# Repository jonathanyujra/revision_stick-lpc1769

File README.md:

# revision_stick-lpc1769
Módulo Stick LPC1769

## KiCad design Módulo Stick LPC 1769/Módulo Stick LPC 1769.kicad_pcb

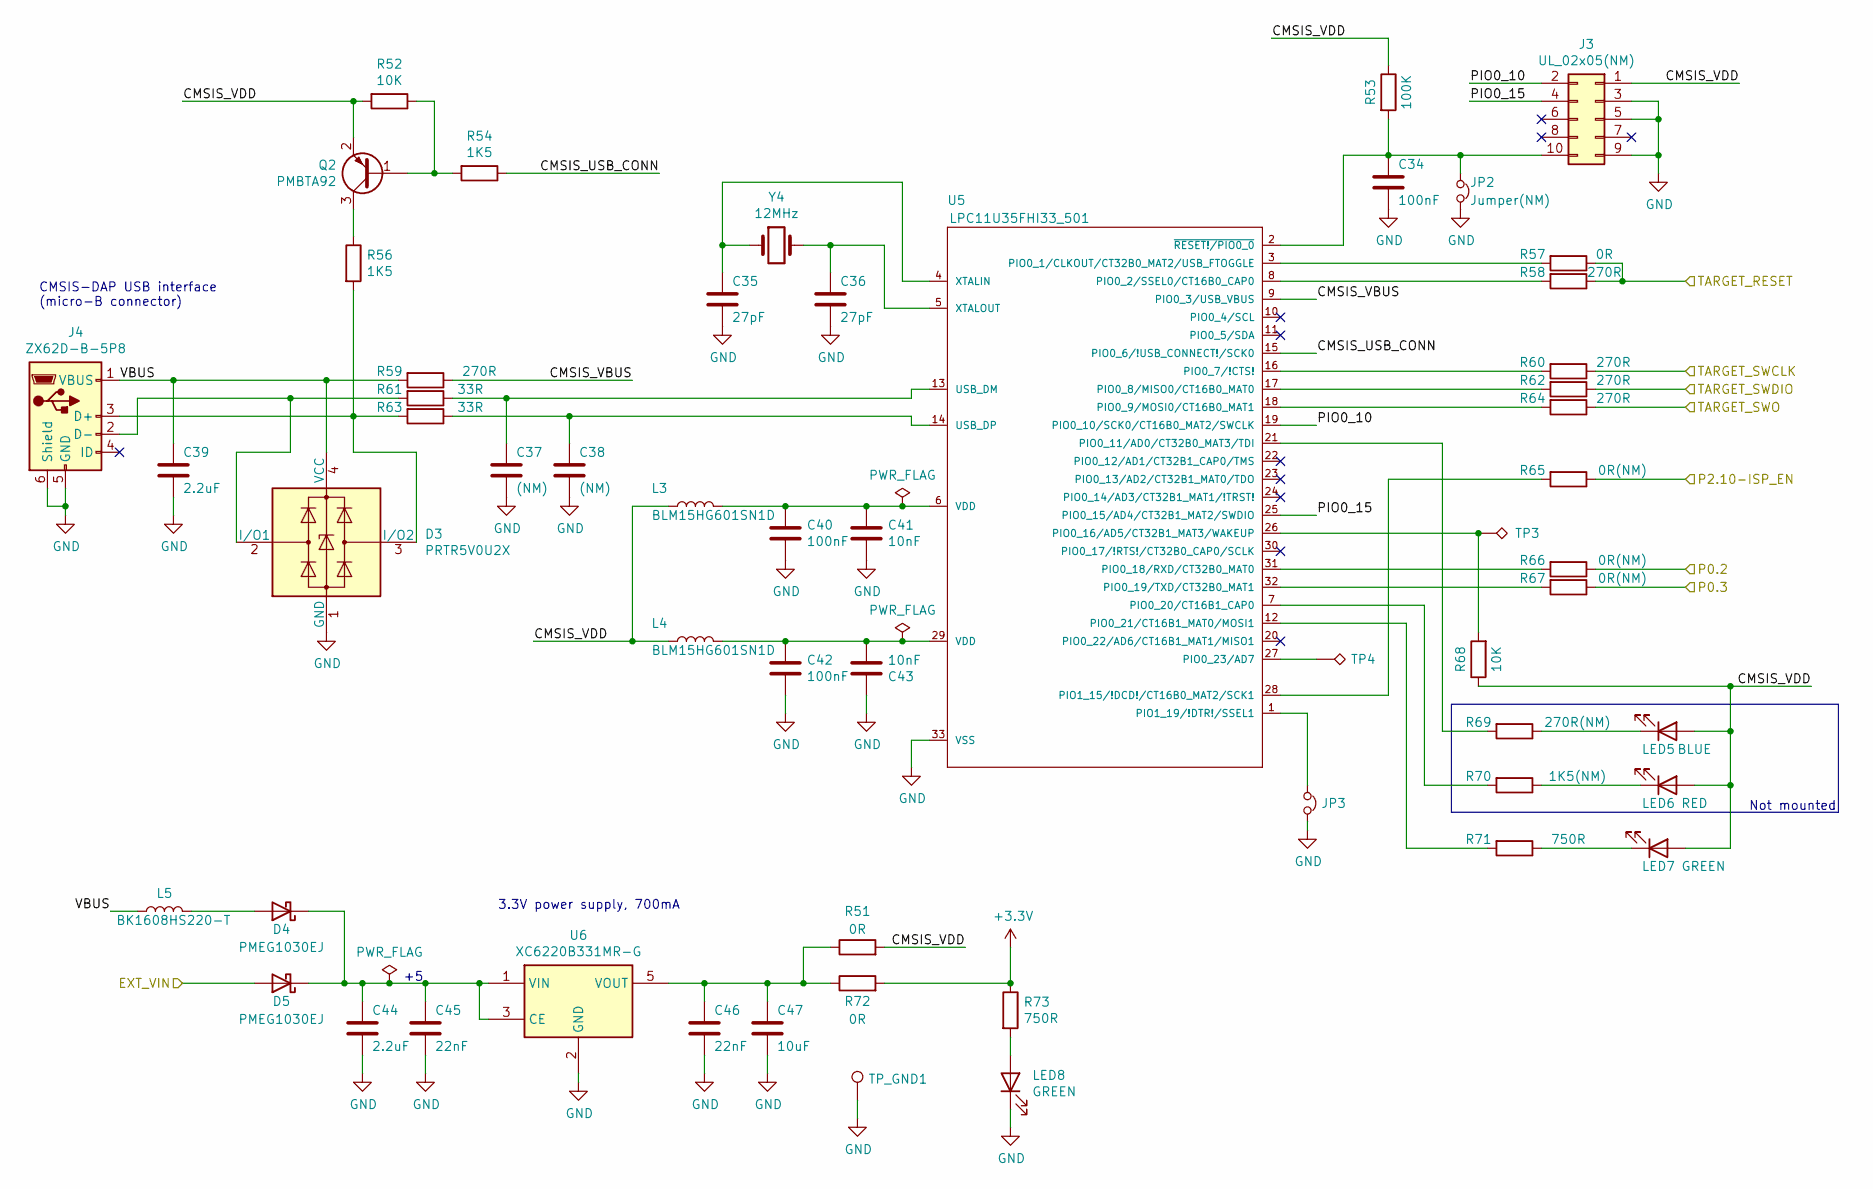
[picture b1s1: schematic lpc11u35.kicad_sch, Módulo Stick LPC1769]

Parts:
C34, C40, C42: 100nF; C_0603; Manufacturer P/N C0603C104Z3VACTU; Digi-Key P/N 399-1100-1-ND
C35, C36: 27pF; C_0603; Manufacturer P/N C0603C270J5GACTU; Digi-Key P/N 399-1054-1-ND
C37, C38: (NM); C_0603
C39, C44: 2.2uF; C_0805; Manufacturer P/N C0805C225K3RAC7800; Digi-Key P/N 399-11941-1-ND
C41, C43: 10nF; C_0603; Manufacturer P/N C0603C103K3RACTU; Digi-Key P/N 399-7840-1-ND
C45, C46: 22nF; C_0603; Manufacturer P/N C0603C223K3RACTU; Digi-Key P/N 399-1094-1-ND
C47: 10uF; C_0805; Manufacturer P/N C0805C106K3PAC7800; Digi-Key P/N 399-11939-1-ND
D3: PRTR5V0U2X; SOT-143; Manufacturer P/N PRTR5V0U2X,215; Digi-Key P/N 1727-3884-1-ND
D4, D5: PMEG1030EJ; D_SOD-323F; Manufacturer P/N PMEG1030EJ,115; Digi-Key P/N 1727-3852-1-ND
J3: UL_02x05(NM); M50-3600542
J4: ZX62D-B-5P8; USB_Micro-B; Manufacturer P/N 10118193-0001LF; Digi-Key P/N 609-4616-2-ND
JP2: Jumper(NM); Pin_Header_Straight_1x02_Pitch2.54mm
JP3: Jumper; Pin_Header_Straight_1x02_Pitch2.54mm_SMD_Pin1Right; Manufacturer P/N M50-3630242; Digi-Key P/N 952-3606-ND
L3, L4: BLM15HG601SN1D; L_0402; Manufacturer P/N BLM15HG601SN1D; Digi-Key P/N 490-3998-1-ND
L5: BK1608HS220-T; L_0603; Manufacturer P/N BK1608HS220-T; Digi-Key P/N 587-1869-1-ND
LED5: BLUE; LED_0603; Manufacturer P/N 150060BS55040; Digi-Key P/N 732-12013-1-ND
LED6: RED; LED_0603; Manufacturer P/N 150060RS55040; Digi-Key P/N 732-12015-1-ND
LED7, LED8: GREEN; LED_0603; Manufacturer P/N 150060VS55040; Digi-Key P/N 732-12017-1-ND
Q2: PMBTA92; SOT-23; Manufacturer P/N PMBTA92,215; Digi-Key P/N 1727-2966-1-ND
R51, R57, R72: 0R; R_0603; Manufacturer P/N RC0603JR-070RL; Digi-Key P/N 311-0.0GRCT-ND
R52, R68: 10K; R_0603; Manufacturer P/N RC0603JR-0710KL; Digi-Key P/N 311-10KGRCT-ND
R53: 100K; R_0603; Manufacturer P/N RC0603JR-07100KL; Digi-Key P/N 311-100KGRCT-ND
R54, R56: 1K5; R_0603; Manufacturer P/N RC0603JR-071K5L; Digi-Key P/N 311-1.5KGRCT-ND
R58, R59, R60, R62, R64: 270R; R_0603; Manufacturer P/N RC0603JR-07270RL; Digi-Key P/N 311-270GRCT-ND
R61, R63: 33R; R_0603; Manufacturer P/N RC0603JR-0733RL; Digi-Key P/N 311-33GRCT-ND
R65, R66, R67: 0R(NM); R_0603
R69: 270R(NM); R_0603
R70: 1K5(NM); R_0603
R71, R73: 750R; R_0603; Manufacturer P/N RC0603JR-07750RL; Digi-Key P/N 311-750GRCT-ND
TP3, TP4: TestPoint; TestPoint-SMD-S
TP_GND1: TestPoint; TestPoint-SMD-S
U5: LPC11U35FHI33_501; QFN65-8X8_M-33N; Manufacturer P/N LPC11U35FHI33/501; Digi-Key P/N 568-9586-ND
U6: XC6220B331MR-G; SOT-25; Manufacturer P/N XC6220B331MR-G; Digi-Key P/N 893-1133-1-ND
Y4: 12MHz; Crystal_SMD_HC49-SD; Manufacturer P/N ECS-120-20-5PX-TR; Digi-Key P/N XC2080CT-ND

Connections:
+3V3: R72.2, R73.1; also elsewhere on the board
/EXT_VIN: D5.2 (A); also elsewhere on the board
/LPC11U35/CMSIS_USB_CONN: R54.1, U5.15 (PIO0_6/!USB_CONNECT!/SCK0)
/LPC11U35/CMSIS_VBUS: R59.1, U5.9 (PIO0_3/USB_VBUS)
/LPC11U35/CMSIS_VDD: J3.1, L3.1, L4.1, LED5.2 (A), LED6.2 (A), LED7.2 (A), Q2.2 (E), R51.2, R52.2, R53.1, R68.1
/LPC11U35/PIO0_10: J3.2, U5.19 (PIO0_10/SCK0/CT16B0_MAT2/SWCLK)
/LPC11U35/PIO0_15: J3.4, U5.25 (PIO0_15/AD4/CT32B1_MAT2/SWDIO)
/LPC11U35/TARGET_SWCLK: R60.1; also elsewhere on the board
/LPC11U35/TARGET_SWDIO: R62.1; also elsewhere on the board
/LPC11U35/TARGET_SWO: R64.1; also elsewhere on the board
/P0.2: R66.1; also elsewhere on the board
/P0.3: R67.1; also elsewhere on the board
/P2.10-ISP_EN: R65.1; also elsewhere on the board
/TARGET_RESET: R57.1, R58.1; also elsewhere on the board
GND: C34.2, C35.2, C36.2, C37.2, C38.2, C39.2, C40.2, C41.2, C42.2, C43.1, C44.2, C45.2, C46.2, C47.2, D3.1 (GND), J3.3, J3.5, J3.9, J4.5 (GND), J4.6 (Shield), JP2.2, JP3.2, LED8.1 (K), TP_GND1.1, U5.33 (VSS), U6.2 (GND); also elsewhere on the board
unnamed: C34.1, J3.10, JP2.1, R53.2, U5.2 (~RESET!/PIO0_0)
unnamed: C35.1, U5.4 (XTALIN), Y4.1
unnamed: C36.1, U5.5 (XTALOUT), Y4.2
unnamed: C37.1, R61.1, U5.13 (USB_DM)
unnamed: C38.1, R63.1, U5.14 (USB_DP)
unnamed: C39.1, D3.4 (VCC), J4.1 (VBUS), L5.1, R59.2
unnamed: C40.1, C41.1, L3.2, U5.6 (VDD)
unnamed: C42.1, C43.2, L4.2, U5.29 (VDD)
unnamed: C44.1, C45.1, D4.1 (K), D5.1 (K), U6.1 (VIN), U6.3 (CE)
unnamed: C46.1, C47.1, R51.1, R72.1, U6.5 (VOUT)
unnamed: D3.2 (I/O1), J4.2 (D-), R61.2
unnamed: D3.3 (I/O2), J4.3 (D+), R56.2, R63.2
unnamed: D4.2 (A), L5.2
unnamed: JP3.1, U5.1 (PIO1_19/!DTR!/SSEL1)
unnamed: LED5.1 (K), R69.1
unnamed: LED6.1 (K), R70.1
unnamed: LED7.1 (K), R71.1
unnamed: LED8.2 (A), R73.2
unnamed: Q2.1 (B), R52.1, R54.2
unnamed: Q2.3 (C), R56.1
unnamed: R57.2, U5.3 (PIO0_1/CLKOUT/CT32B0_MAT2/USB_FTOGGLE)
unnamed: R58.2, U5.8 (PIO0_2/SSEL0/CT16B0_CAP0)
unnamed: R60.2, U5.16 (PIO0_7/!CTS!)
unnamed: R62.2, U5.17 (PIO0_8/MISO0/CT16B0_MAT0)
unnamed: R64.2, U5.18 (PIO0_9/MOSI0/CT16B0_MAT1)
unnamed: R65.2, U5.28 (PIO1_15/!DCD!/CT16B0_MAT2/SCK1)
unnamed: R66.2, U5.31 (PIO0_18/RXD/CT32B0_MAT0)
unnamed: R67.2, U5.32 (PIO0_19/TXD/CT32B0_MAT1)
unnamed: R68.2, TP3.1, U5.26 (PIO0_16/AD5/CT32B1_MAT3/WAKEUP)
unnamed: R69.2, U5.21 (PIO0_11/AD0/CT32B0_MAT3/TDI)
unnamed: R70.2, U5.7 (PIO0_20/CT16B1_CAP0)
unnamed: R71.2, U5.12 (PIO0_21/CT16B1_MAT0/MOSI1)
unnamed: TP4.1, U5.27 (PIO0_23/AD7)

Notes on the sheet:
CMSIS-DAP USB interface (micro-B connector)
3.3V power supply, 700mA
Not mounted

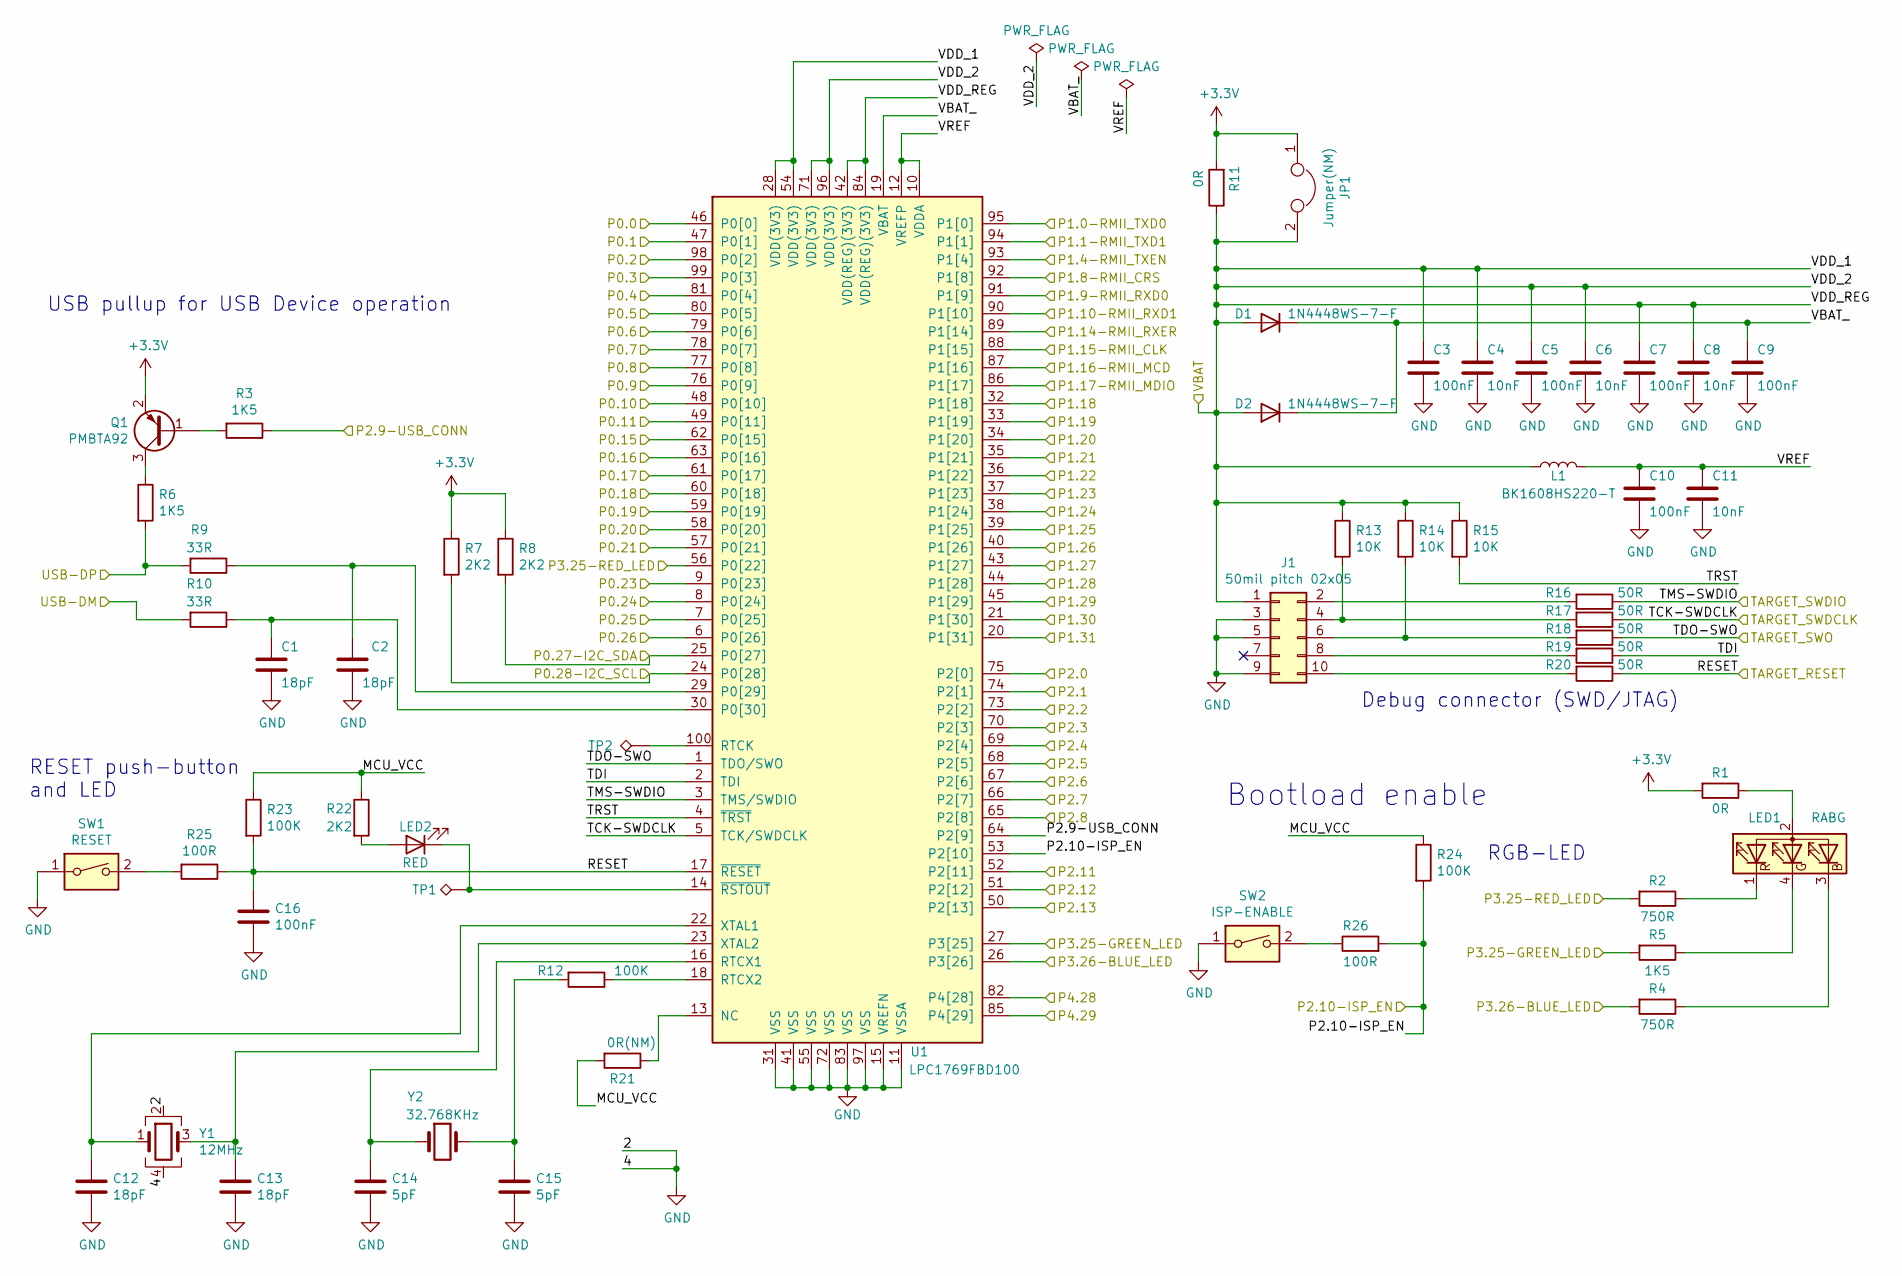
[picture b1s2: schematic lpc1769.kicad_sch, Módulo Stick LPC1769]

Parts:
C1, C2, C12, C13: 18pF; C_0603; Manufacturer P/N C0603C180J5GACTU; Digi-Key P/N 399-1052-1-ND
C3, C5, C7, C9, C10, C16: 100nF; C_0603; Manufacturer P/N C0603C104Z3VACTU; Digi-Key P/N 399-1100-1-ND
C4, C6, C8, C11: 10nF; C_0603; Manufacturer P/N C0603C103K3RACTU; Digi-Key P/N 399-7840-1-ND
C14, C15: 5pF; C_0603; Manufacturer P/N CBR06C509C5GAC; Digi-Key P/N 399-17324-1-ND
D1, D2: 1N4448WS-7-F; D_SOD-323; Manufacturer P/N 1N4448WS-7-F; Digi-Key P/N 1N4448WS-FDICT-ND
J1: 50mil pitch 02x05; M50-3600542; Manufacturer P/N M50-3600542; Digi-Key P/N 952-1389-ND
JP1: Jumper(NM); Pin_Header_Straight_1x02_Pitch2.54mm
L1: BK1608HS220-T; L_0603; Manufacturer P/N BK1608HS220-T; Digi-Key P/N 587-1869-1-ND
LED1: RABG; LED_RGB_1210; Manufacturer P/N AAA3528SEEZGKQBKS; Digi-Key P/N 754-1973-1-ND
LED2: RED; LED_0603; Manufacturer P/N 150060RS55040; Digi-Key P/N 732-12015-1-ND
Q1: PMBTA92; SOT-23; Manufacturer P/N PMBTA92,215; Digi-Key P/N 1727-2966-1-ND
R1, R11: 0R; R_0603; Manufacturer P/N RC0603JR-070RL; Digi-Key P/N 311-0.0GRCT-ND
R2, R4: 750R; R_0603; Manufacturer P/N RC0603JR-07750RL; Digi-Key P/N 311-750GRCT-ND
R3, R5, R6: 1K5; R_0603; Manufacturer P/N RC0603JR-071K5L; Digi-Key P/N 311-1.5KGRCT-ND
R7, R8, R22: 2K2; R_0603; Manufacturer P/N RC0603JR-072K2L; Digi-Key P/N 311-2.2KGRCT-ND
R9, R10: 33R; R_0603; Manufacturer P/N RC0603JR-0733RL; Digi-Key P/N 311-33GRCT-ND
R12, R23, R24: 100K; R_0603; Manufacturer P/N RC0603JR-07100KL; Digi-Key P/N 311-100KGRCT-ND
R13, R14, R15: 10K; R_0603; Manufacturer P/N RC0603JR-0710KL; Digi-Key P/N 311-10KGRCT-ND
R16, R17, R18, R19, R20: 50R; R_0603; Manufacturer P/N CRCW060350R0FKEA; Digi-Key P/N 541-3318-1-ND
R21: 0R(NM); R_0603
R25, R26: 100R; R_0603; Manufacturer P/N RC0603JR-07100RL; Digi-Key P/N 311-100GRCT-ND
SW1: RESET; SW_2.80x4.60mm; Manufacturer P/N TL6330AF200Q; Digi-Key P/N EG5546CT-ND
SW2: ISP-ENABLE; SW_2.80x4.60mm; Manufacturer P/N TL6330AF200Q; Digi-Key P/N EG5546CT-ND
TP1, TP2: TestPoint; TestPoint-SMD-S
U1: LPC1769FBD100; Manufacturer P/N LPC1769FBD100,551; Digi-Key P/N 568-4966-ND
Y1: 12MHz; Crystal_SMD_3225-4pin_3.2x2.5mm; Manufacturer P/N ECS-120-18-33-AGN-TR; Digi-Key P/N XC2910CT-ND
Y2: 32.768KHz; Crystal_SMD_SeikoEpson_MC146-4pin_6.7x1.5mm; Manufacturer P/N MC-146 32.7680KA-A5: PURE SN; Digi-Key P/N SER4301CT-ND

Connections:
+3V3: JP1.1, Q1.2 (E), R1.2, R7.1, R8.1, R11.2; also elsewhere on the board
/Expansion_connector/P0.15: U1.62 (P0[15]); also elsewhere on the board
/Expansion_connector/P0.16: U1.63 (P0[16]); also elsewhere on the board
/Expansion_connector/P0.17: U1.61 (P0[17]); also elsewhere on the board
/Expansion_connector/P0.18: U1.60 (P0[18]); also elsewhere on the board
/Expansion_connector/P0.21: U1.57 (P0[21]); also elsewhere on the board
/Expansion_connector/P0.22-RED_LED: R2.2, U1.56 (P0[22]); also elsewhere on the board
/Expansion_connector/P0.23: U1.9 (P0[23]); also elsewhere on the board
/Expansion_connector/P0.24: U1.8 (P0[24]); also elsewhere on the board
/Expansion_connector/P0.25: U1.7 (P0[25]); also elsewhere on the board
/Expansion_connector/P0.26: U1.6 (P0[26]); also elsewhere on the board
/Expansion_connector/P0.27-I2C_SDA: R8.2, U1.25 (P0[27]); also elsewhere on the board
/Expansion_connector/P0.28-I2C_SCL: R7.2, U1.24 (P0[28]); also elsewhere on the board
/Expansion_connector/P1.18: U1.32 (P1[18]); also elsewhere on the board
/Expansion_connector/P1.19: U1.33 (P1[19]); also elsewhere on the board
/Expansion_connector/P1.20: U1.34 (P1[20]); also elsewhere on the board
/Expansion_connector/P1.21: U1.35 (P1[21]); also elsewhere on the board
/Expansion_connector/P1.22: U1.36 (P1[22]); also elsewhere on the board
/Expansion_connector/P1.23: U1.37 (P1[23]); also elsewhere on the board
/Expansion_connector/P1.24: U1.38 (P1[24]); also elsewhere on the board
/Expansion_connector/P1.25: U1.39 (P1[25]); also elsewhere on the board
/Expansion_connector/P1.26: U1.40 (P1[26]); also elsewhere on the board
/Expansion_connector/P1.27: U1.43 (P1[27]); also elsewhere on the board
/Expansion_connector/P1.28: U1.44 (P1[28]); also elsewhere on the board
/Expansion_connector/P1.29: U1.45 (P1[29]); also elsewhere on the board
/Expansion_connector/P1.30: U1.21 (P1[30]); also elsewhere on the board
/Expansion_connector/P1.31: U1.20 (P1[31]); also elsewhere on the board
/Expansion_connector/P2.0: U1.75 (P2[0]); also elsewhere on the board
/Expansion_connector/P2.1: U1.74 (P2[1]); also elsewhere on the board
/Expansion_connector/P2.2: U1.73 (P2[2]); also elsewhere on the board
/Expansion_connector/P2.3: U1.70 (P2[3]); also elsewhere on the board
/Expansion_connector/P2.4: U1.69 (P2[4]); also elsewhere on the board
/Expansion_connector/P2.5: U1.68 (P2[5]); also elsewhere on the board
/Expansion_connector/P2.6: U1.67 (P2[6]); also elsewhere on the board
/Expansion_connector/P2.7: U1.66 (P2[7]); also elsewhere on the board
/Expansion_connector/P2.8: U1.65 (P2[8]); also elsewhere on the board
/Expansion_connector/P2.11: U1.52 (P2[11]); also elsewhere on the board
/Expansion_connector/P2.12: U1.51 (P2[12]); also elsewhere on the board
/Expansion_connector/P2.13: U1.50 (P2[13]); also elsewhere on the board
/Expansion_connector/P3.25-GREEN_LED: R5.2, U1.27 (P3[25]); also elsewhere on the board
/Expansion_connector/P3.26-BLUE_LED: R4.2, U1.26 (P3[26]); also elsewhere on the board
/Expansion_connector/P4.28: U1.82 (P4[28]); also elsewhere on the board
/Expansion_connector/P4.29: U1.85 (P4[29]); also elsewhere on the board
/LAN8720/P1.0-RMII_TXD0: U1.95 (P1[0]); also elsewhere on the board
/LAN8720/P1.1-RMII_TXD1: U1.94 (P1[1]); also elsewhere on the board
/LAN8720/P1.4-RMII_TXEN: U1.93 (P1[4]); also elsewhere on the board
/LAN8720/P1.8-RMII_CRS: U1.92 (P1[8]); also elsewhere on the board
/LAN8720/P1.9-RMII_RXD0: U1.91 (P1[9]); also elsewhere on the board
/LAN8720/P1.10-RMII_RXD1: U1.90 (P1[10]); also elsewhere on the board
/LAN8720/P1.14-RMII_RXER: U1.89 (P1[14]); also elsewhere on the board
/LAN8720/P1.15-RMII_CLK: U1.88 (P1[15]); also elsewhere on the board
/LAN8720/P1.16-RMII_MCD: U1.87 (P1[16]); also elsewhere on the board
/LAN8720/P1.17-RMII_MDIO: U1.86 (P1[17]); also elsewhere on the board
/LPC11U35/TARGET_SWCLK: R17.1, U1.5 (TCK/SWDCLK); also elsewhere on the board
/LPC11U35/TARGET_SWDIO: R16.1, U1.3 (TMS/SWDIO); also elsewhere on the board
/LPC11U35/TARGET_SWO: R18.1, U1.1 (TDO/SWO); also elsewhere on the board
/LPC1769/MCU_VCC: R21.2, R22.1, R23.1, R24.1
/LPC1769/TDI: R19.1, U1.2 (TDI)
/LPC1769/TRST: R15.2, U1.4 (~TRST)
/LPC1769/VBAT_: C9.1, D1.1 (K), D2.1 (K), U1.19 (VBAT)
/LPC1769/VREF: C10.1, C11.1, L1.2, U1.10 (VDDA), U1.12 (VREFP)
/P0.0: U1.46 (P0[0]); also elsewhere on the board
/P0.1: U1.47 (P0[1]); also elsewhere on the board
/P0.2: U1.98 (P0[2]); also elsewhere on the board
/P0.3: U1.99 (P0[3]); also elsewhere on the board
/P0.4: U1.81 (P0[4]); also elsewhere on the board
/P0.5: U1.80 (P0[5]); also elsewhere on the board
/P0.6: U1.79 (P0[6]); also elsewhere on the board
/P0.7: U1.78 (P0[7]); also elsewhere on the board
/P0.8: U1.77 (P0[8]); also elsewhere on the board
/P0.9: U1.76 (P0[9]); also elsewhere on the board
/P0.10: U1.48 (P0[10]); also elsewhere on the board
/P0.11: U1.49 (P0[11]); also elsewhere on the board
/P0.19: U1.59 (P0[19]); also elsewhere on the board
/P0.20: U1.58 (P0[20]); also elsewhere on the board
/P2.9-USB_CONN: R3.1, U1.64 (P2[9]); also elsewhere on the board
/P2.10-ISP_EN: R24.2, R26.2, U1.53 (P2[10]); also elsewhere on the board
/TARGET_RESET: C16.1, R20.1, R23.2, R25.1, U1.17 (~RESET); also elsewhere on the board
/USB-DM: R10.2; also elsewhere on the board
/USB-DP: R6.2, R9.2; also elsewhere on the board
GND: C1.2, C2.2, C3.2, C4.2, C5.2, C6.2, C7.2, C8.2, C9.2, C10.2, C11.2, C12.2, C13.2, C14.2, C15.2, C16.2, J1.3, J1.5, J1.9, SW1.1, SW2.1, U1.11 (VSSA), U1.15 (VREFN), U1.31 (VSS), U1.41 (VSS), U1.55 (VSS), U1.72 (VSS), U1.83 (VSS), U1.97 (VSS), Y1.2, Y1.4; also elsewhere on the board
unnamed: C1.1, R10.1, U1.30 (P0[30])
unnamed: C2.1, R9.1, U1.29 (P0[29])
unnamed: C12.1, U1.22 (XTAL1), Y1.1
unnamed: C13.1, U1.23 (XTAL2), Y1.3
unnamed: C14.1, U1.16 (RTCX1), Y2.1
unnamed: C15.1, R12.2, Y2.2
unnamed: J1.2, R16.2
unnamed: J1.4, R13.2, R17.2
unnamed: J1.6, R14.2, R18.2
unnamed: J1.8, R19.2
unnamed: J1.10, R20.2
unnamed: LED1.1 (RK), R2.1
unnamed: LED1.2 (A), R1.1
unnamed: LED1.3 (BK), R4.1
unnamed: LED1.4 (GK), R5.1
unnamed: LED2.1 (K), TP1.1, U1.14 (~RSTOUT)
unnamed: LED2.2 (A), R22.2
unnamed: Q1.1 (B), R3.2
unnamed: Q1.3 (C), R6.1
unnamed: R12.1, U1.18 (RTCX2)
unnamed: R21.1, U1.13 (NC)
unnamed: R25.2, SW1.2
unnamed: R26.1, SW2.2
unnamed: TP2.1, U1.100 (RTCK)

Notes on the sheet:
Debug connector (SWD/JTAG)
RGB-LED
USB pullup for USB Device operation
RESET push-button and LED
Bootload enable

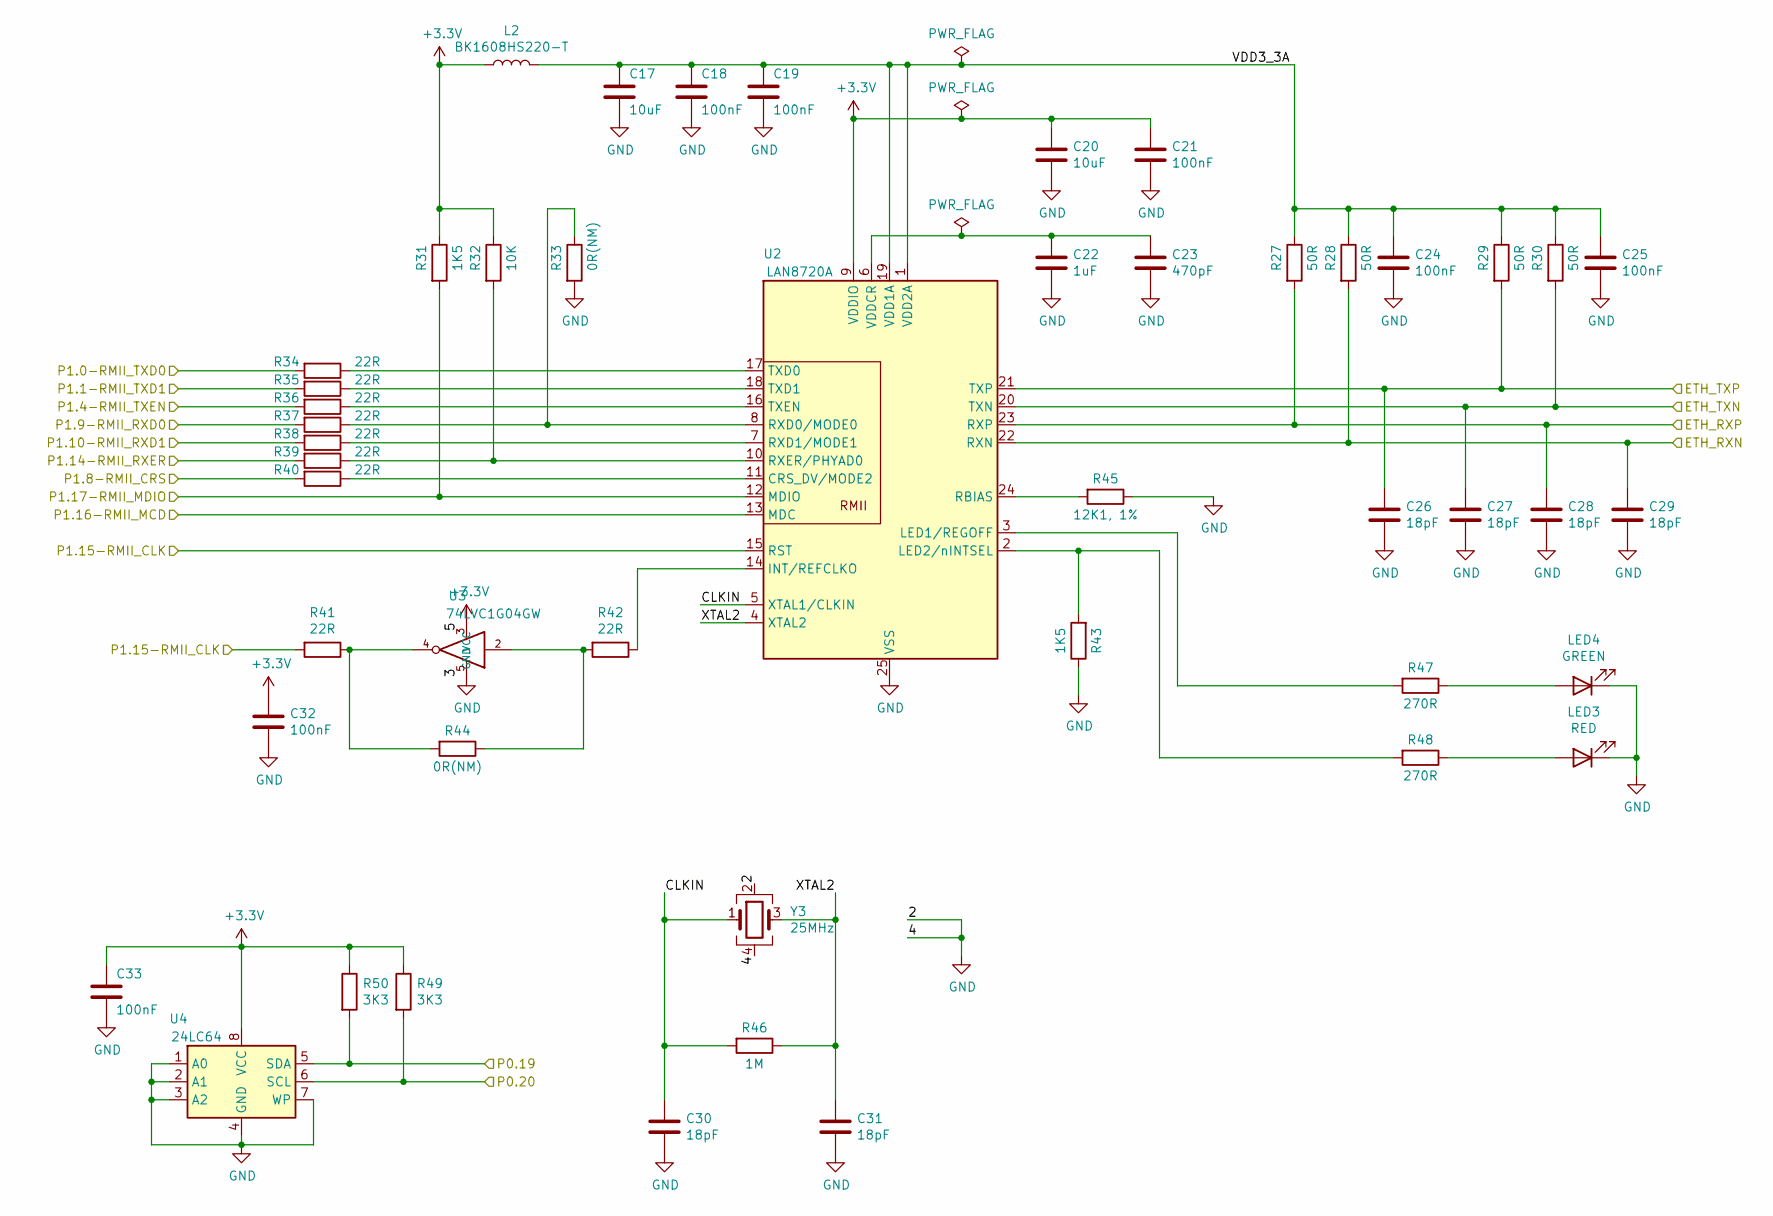
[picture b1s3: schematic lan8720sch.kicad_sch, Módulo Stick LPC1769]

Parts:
C17, C20: 10uF; C_0805; Manufacturer P/N C0805C106K3PAC7800; Digi-Key P/N 399-11939-1-ND
C18, C19, C21, C24, C25, C32, C33: 100nF; C_0603; Manufacturer P/N C0603C104Z3VACTU; Digi-Key P/N 399-1100-1-ND
C22: 1uF; C_0805; Manufacturer P/N C0805C105K3RACTU; Digi-Key P/N 399-8004-1-ND
C23: 470pF; C_0603; Manufacturer P/N C0603C471K5RACTU; Digi-Key P/N 399-1075-1-ND
C26, C27, C28, C29, C30, C31: 18pF; C_0603; Manufacturer P/N C0603C180J5GACTU; Digi-Key P/N 399-1052-1-ND
L2: BK1608HS220-T; L_0603; Manufacturer P/N BK1608HS220-T; Digi-Key P/N 587-1869-1-ND
LED3: RED; LED_0603; Manufacturer P/N 150060RS55040; Digi-Key P/N 732-12015-1-ND
LED4: GREEN; LED_0603; Manufacturer P/N 150060VS55040; Digi-Key P/N 732-12017-1-ND
R27, R28, R29, R30: 50R; R_0603; Manufacturer P/N CRCW060350R0FKEA; Digi-Key P/N 541-3318-1-ND
R31, R43: 1K5; R_0603; Manufacturer P/N RC0603JR-071K5L; Digi-Key P/N 311-1.5KGRCT-ND
R32: 10K; R_0603; Manufacturer P/N RC0603JR-0710KL; Digi-Key P/N 311-10KGRCT-ND
R33, R44: 0R(NM); R_0603
R34, R35, R36, R37, R38, R39, R40, R41, R42: 22R; R_0603; Manufacturer P/N RC0603JR-0722RL; Digi-Key P/N 311-22GRCT-ND
R45: 12K1, 1%; R_0603; Manufacturer P/N RC0603FR-0712K1L; Digi-Key P/N 311-12.1KHRCT-ND
R46: 1M; R_0603; Manufacturer P/N RC0603JR-071ML; Digi-Key P/N 311-1.0MGRCT-ND
R47, R48: 270R; R_0603; Manufacturer P/N RC0603JR-07270RL; Digi-Key P/N 311-270GRCT-ND
R49, R50: 3K3; R_0603; Manufacturer P/N RC0603JR-073K3L; Digi-Key P/N 311-3.3KGRCT-ND
U2: LAN8720A; LAN8720A-CP; Manufacturer P/N LAN8720A-CP; Digi-Key P/N 638-1080-ND
U3: 74LVC1G04GW; SOT-353_SC-70-5; Manufacturer P/N 74LVC1G04GW,125; Digi-Key P/N 1727-2871-1-ND
U4: 24LC64; 24LC64T-I&slash_SN; Manufacturer P/N 24LC64T-I/SN; Digi-Key P/N 24LC64T-I/SNCT-ND
Y3: 25MHz; Crystal_SMD_3225-4pin_3.2x2.5mm; Manufacturer P/N ECS-250-8-33-JGN-TR; Digi-Key P/N XC2650CT-ND

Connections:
+3V3: C20.1, C21.1, C32.1, C33.1, L2.1, R31.1, R32.1, R49.1, R50.1, U2.9 (VDDIO), U3.3 (GND), U4.8 (VCC); also elsewhere on the board
/ETH_RXN: C29.1, R28.2, U2.22 (RXN); also elsewhere on the board
/ETH_RXP: C28.1, R27.2, U2.23 (RXP); also elsewhere on the board
/ETH_TXN: C27.1, R30.2, U2.20 (TXN); also elsewhere on the board
/ETH_TXP: C26.1, R29.2, U2.21 (TXP); also elsewhere on the board
/LAN8720/P1.0-RMII_TXD0: R34.2; also elsewhere on the board
/LAN8720/P1.1-RMII_TXD1: R35.2; also elsewhere on the board
/LAN8720/P1.4-RMII_TXEN: R36.2; also elsewhere on the board
/LAN8720/P1.8-RMII_CRS: R40.2; also elsewhere on the board
/LAN8720/P1.9-RMII_RXD0: R37.2; also elsewhere on the board
/LAN8720/P1.10-RMII_RXD1: R38.2; also elsewhere on the board
/LAN8720/P1.14-RMII_RXER: R39.2; also elsewhere on the board
/LAN8720/P1.15-RMII_CLK: R41.2, U2.15 (RST); also elsewhere on the board
/LAN8720/P1.16-RMII_MCD: U2.13 (MDC); also elsewhere on the board
/LAN8720/P1.17-RMII_MDIO: R31.2, U2.12 (MDIO); also elsewhere on the board
/LAN8720/VDD3_3A: C17.1, C18.1, C19.1, C24.1, C25.1, L2.2, R27.1, R28.1, R29.1, R30.1, U2.1 (VDD2A), U2.19 (VDD1A)
/P0.19: R50.2, U4.5 (SDA); also elsewhere on the board
/P0.20: R49.2, U4.6 (SCL); also elsewhere on the board
GND: C17.2, C18.2, C19.2, C20.2, C21.2, C22.2, C23.2, C24.2, C25.2, C26.2, C27.2, C28.2, C29.2, C30.2, C31.2, C32.2, C33.2, LED3.1 (K), LED4.1 (K), R33.2, R43.1, R45.1, U2.25 (VSS), U3.5 (VCC), U4.1 (A0), U4.2 (A1), U4.3 (A2), U4.4 (GND), U4.7 (WP), Y3.2, Y3.4; also elsewhere on the board
unnamed: C22.1, C23.1, U2.6 (VDDCR)
unnamed: C30.1, R46.2, U2.5 (XTAL1/CLKIN), Y3.1
unnamed: C31.1, R46.1, U2.4 (XTAL2), Y3.3
unnamed: LED3.2 (A), R48.1
unnamed: LED4.2 (A), R47.1
unnamed: R32.2, R39.1, U2.10 (RXER/PHYAD0)
unnamed: R33.1, R37.1, U2.8 (RXD0/MODE0)
unnamed: R34.1, U2.17 (TXD0)
unnamed: R35.1, U2.18 (TXD1)
unnamed: R36.1, U2.16 (TXEN)
unnamed: R38.1, U2.7 (RXD1/MODE1)
unnamed: R40.1, U2.11 (CRS_DV/MODE2)
unnamed: R41.1, R44.2, U3.4
unnamed: R42.1, U2.14 (INT/REFCLKO)
unnamed: R42.2, R44.1, U3.2
unnamed: R43.2, R48.2, U2.2 (LED2/nINTSEL)
unnamed: R45.2, U2.24 (RBIAS)
unnamed: R47.2, U2.3 (LED1/REGOFF)

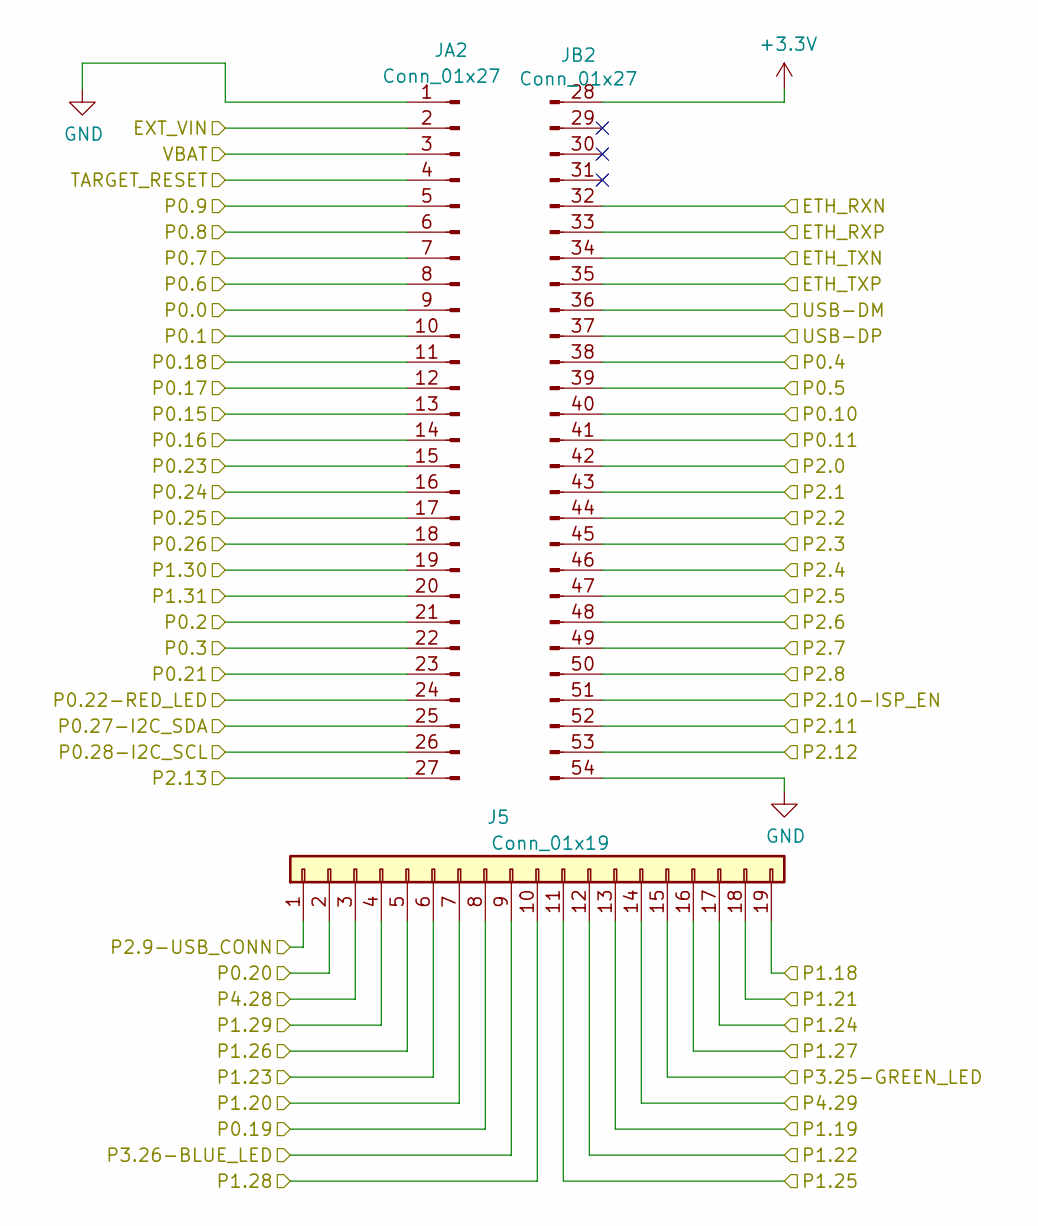
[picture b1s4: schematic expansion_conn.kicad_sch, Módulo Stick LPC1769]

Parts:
J5: Conn_01x19; conn_x19_Pitch2.54mm; Manufacturer P/N 0022284190; Digi-Key P/N WM50014-19-ND
JA2: Conn_01x27; J2_A_1x27_Pitch2.54mm; Manufacturer P/N 0022284270; Digi-Key P/N WM50014-27-ND
JB2: Conn_01x27; J2_B_01x27_Pitch2.54mm; Manufacturer P/N 0022284270; Digi-Key P/N WM50014-27-ND

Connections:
+3V3: JB2.28; also elsewhere on the board
/ETH_RXN: JB2.32; also elsewhere on the board
/ETH_RXP: JB2.33; also elsewhere on the board
/ETH_TXN: JB2.34; also elsewhere on the board
/ETH_TXP: JB2.35; also elsewhere on the board
/EXT_VIN: JA2.2; also elsewhere on the board
/Expansion_connector/P0.15: JA2.13; also elsewhere on the board
/Expansion_connector/P0.16: JA2.14; also elsewhere on the board
/Expansion_connector/P0.17: JA2.12; also elsewhere on the board
/Expansion_connector/P0.18: JA2.11; also elsewhere on the board
/Expansion_connector/P0.21: JA2.23; also elsewhere on the board
/Expansion_connector/P0.22-RED_LED: JA2.24; also elsewhere on the board
/Expansion_connector/P0.23: JA2.15; also elsewhere on the board
/Expansion_connector/P0.24: JA2.16; also elsewhere on the board
/Expansion_connector/P0.25: JA2.17; also elsewhere on the board
/Expansion_connector/P0.26: JA2.18; also elsewhere on the board
/Expansion_connector/P0.27-I2C_SDA: JA2.25; also elsewhere on the board
/Expansion_connector/P0.28-I2C_SCL: JA2.26; also elsewhere on the board
/Expansion_connector/P1.18: J5.19; also elsewhere on the board
/Expansion_connector/P1.19: J5.13; also elsewhere on the board
/Expansion_connector/P1.20: J5.7; also elsewhere on the board
/Expansion_connector/P1.21: J5.18; also elsewhere on the board
/Expansion_connector/P1.22: J5.12; also elsewhere on the board
/Expansion_connector/P1.23: J5.6; also elsewhere on the board
/Expansion_connector/P1.24: J5.17; also elsewhere on the board
/Expansion_connector/P1.25: J5.11; also elsewhere on the board
/Expansion_connector/P1.26: J5.5; also elsewhere on the board
/Expansion_connector/P1.27: J5.16; also elsewhere on the board
/Expansion_connector/P1.28: J5.10; also elsewhere on the board
/Expansion_connector/P1.29: J5.4; also elsewhere on the board
/Expansion_connector/P1.30: JA2.19; also elsewhere on the board
/Expansion_connector/P1.31: JA2.20; also elsewhere on the board
/Expansion_connector/P2.0: JB2.42 (Pin_12); also elsewhere on the board
/Expansion_connector/P2.1: JB2.43 (Pin_13); also elsewhere on the board
/Expansion_connector/P2.2: JB2.44 (Pin_14); also elsewhere on the board
/Expansion_connector/P2.3: JB2.45 (Pin_15); also elsewhere on the board
/Expansion_connector/P2.4: JB2.46 (Pin_16); also elsewhere on the board
/Expansion_connector/P2.5: JB2.47 (Pin_17); also elsewhere on the board
/Expansion_connector/P2.6: JB2.48 (Pin_18); also elsewhere on the board
/Expansion_connector/P2.7: JB2.49 (Pin_19); also elsewhere on the board
/Expansion_connector/P2.8: JB2.50 (Pin_20); also elsewhere on the board
/Expansion_connector/P2.11: JB2.52 (Pin_22); also elsewhere on the board
/Expansion_connector/P2.12: JB2.53 (Pin_23); also elsewhere on the board
/Expansion_connector/P2.13: JA2.27; also elsewhere on the board
/Expansion_connector/P3.25-GREEN_LED: J5.15; also elsewhere on the board
/Expansion_connector/P3.26-BLUE_LED: J5.9; also elsewhere on the board
/Expansion_connector/P4.28: J5.3; also elsewhere on the board
/Expansion_connector/P4.29: J5.14; also elsewhere on the board
/P0.0: JA2.9; also elsewhere on the board
/P0.1: JA2.10; also elsewhere on the board
/P0.2: JA2.21; also elsewhere on the board
/P0.3: JA2.22; also elsewhere on the board
/P0.4: JB2.38; also elsewhere on the board
/P0.5: JB2.39; also elsewhere on the board
/P0.6: JA2.8; also elsewhere on the board
/P0.7: JA2.7; also elsewhere on the board
/P0.8: JA2.6; also elsewhere on the board
/P0.9: JA2.5; also elsewhere on the board
/P0.10: JB2.40; also elsewhere on the board
/P0.11: JB2.41 (Pin_11); also elsewhere on the board
/P0.19: J5.8; also elsewhere on the board
/P0.20: J5.2; also elsewhere on the board
/P2.9-USB_CONN: J5.1; also elsewhere on the board
/P2.10-ISP_EN: JB2.51 (Pin_21); also elsewhere on the board
/TARGET_RESET: JA2.4; also elsewhere on the board
/USB-DM: JB2.36; also elsewhere on the board
/USB-DP: JB2.37; also elsewhere on the board
GND: JA2.1, JB2.54 (Pin_24); also elsewhere on the board

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
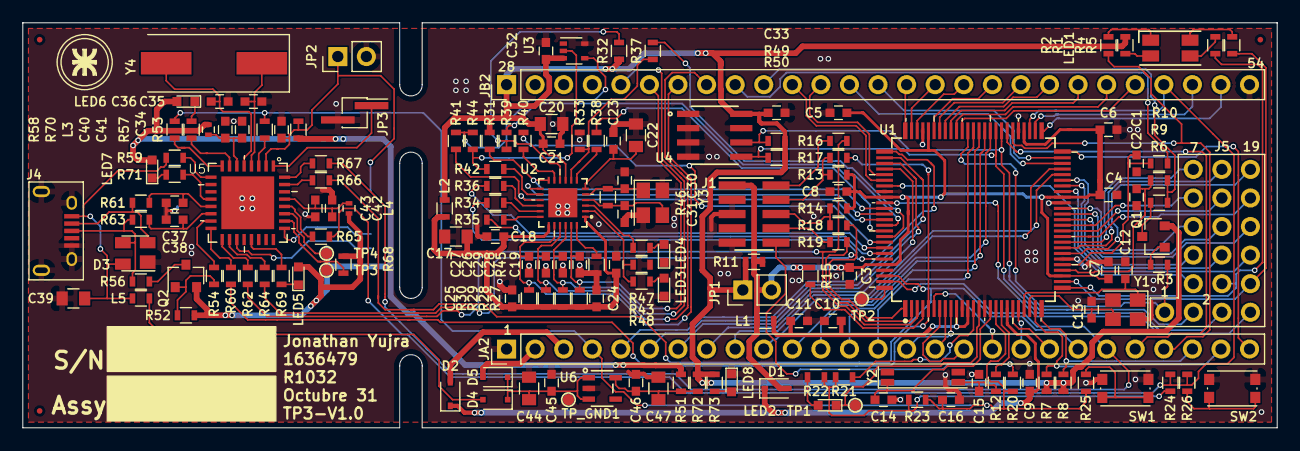
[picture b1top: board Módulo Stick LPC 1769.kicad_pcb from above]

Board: 2 copper layers, 111.5 x 36.0 mm, 166 parts (1 on the bottom side), 169 nets.

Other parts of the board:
LogoUTN.BA: UTN.BA

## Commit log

2025-09-14 <add> [doc] Documentación proyecto

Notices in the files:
parts and their libraries:
Copyright 2016 Accelerated Designs. All rights reserved.
